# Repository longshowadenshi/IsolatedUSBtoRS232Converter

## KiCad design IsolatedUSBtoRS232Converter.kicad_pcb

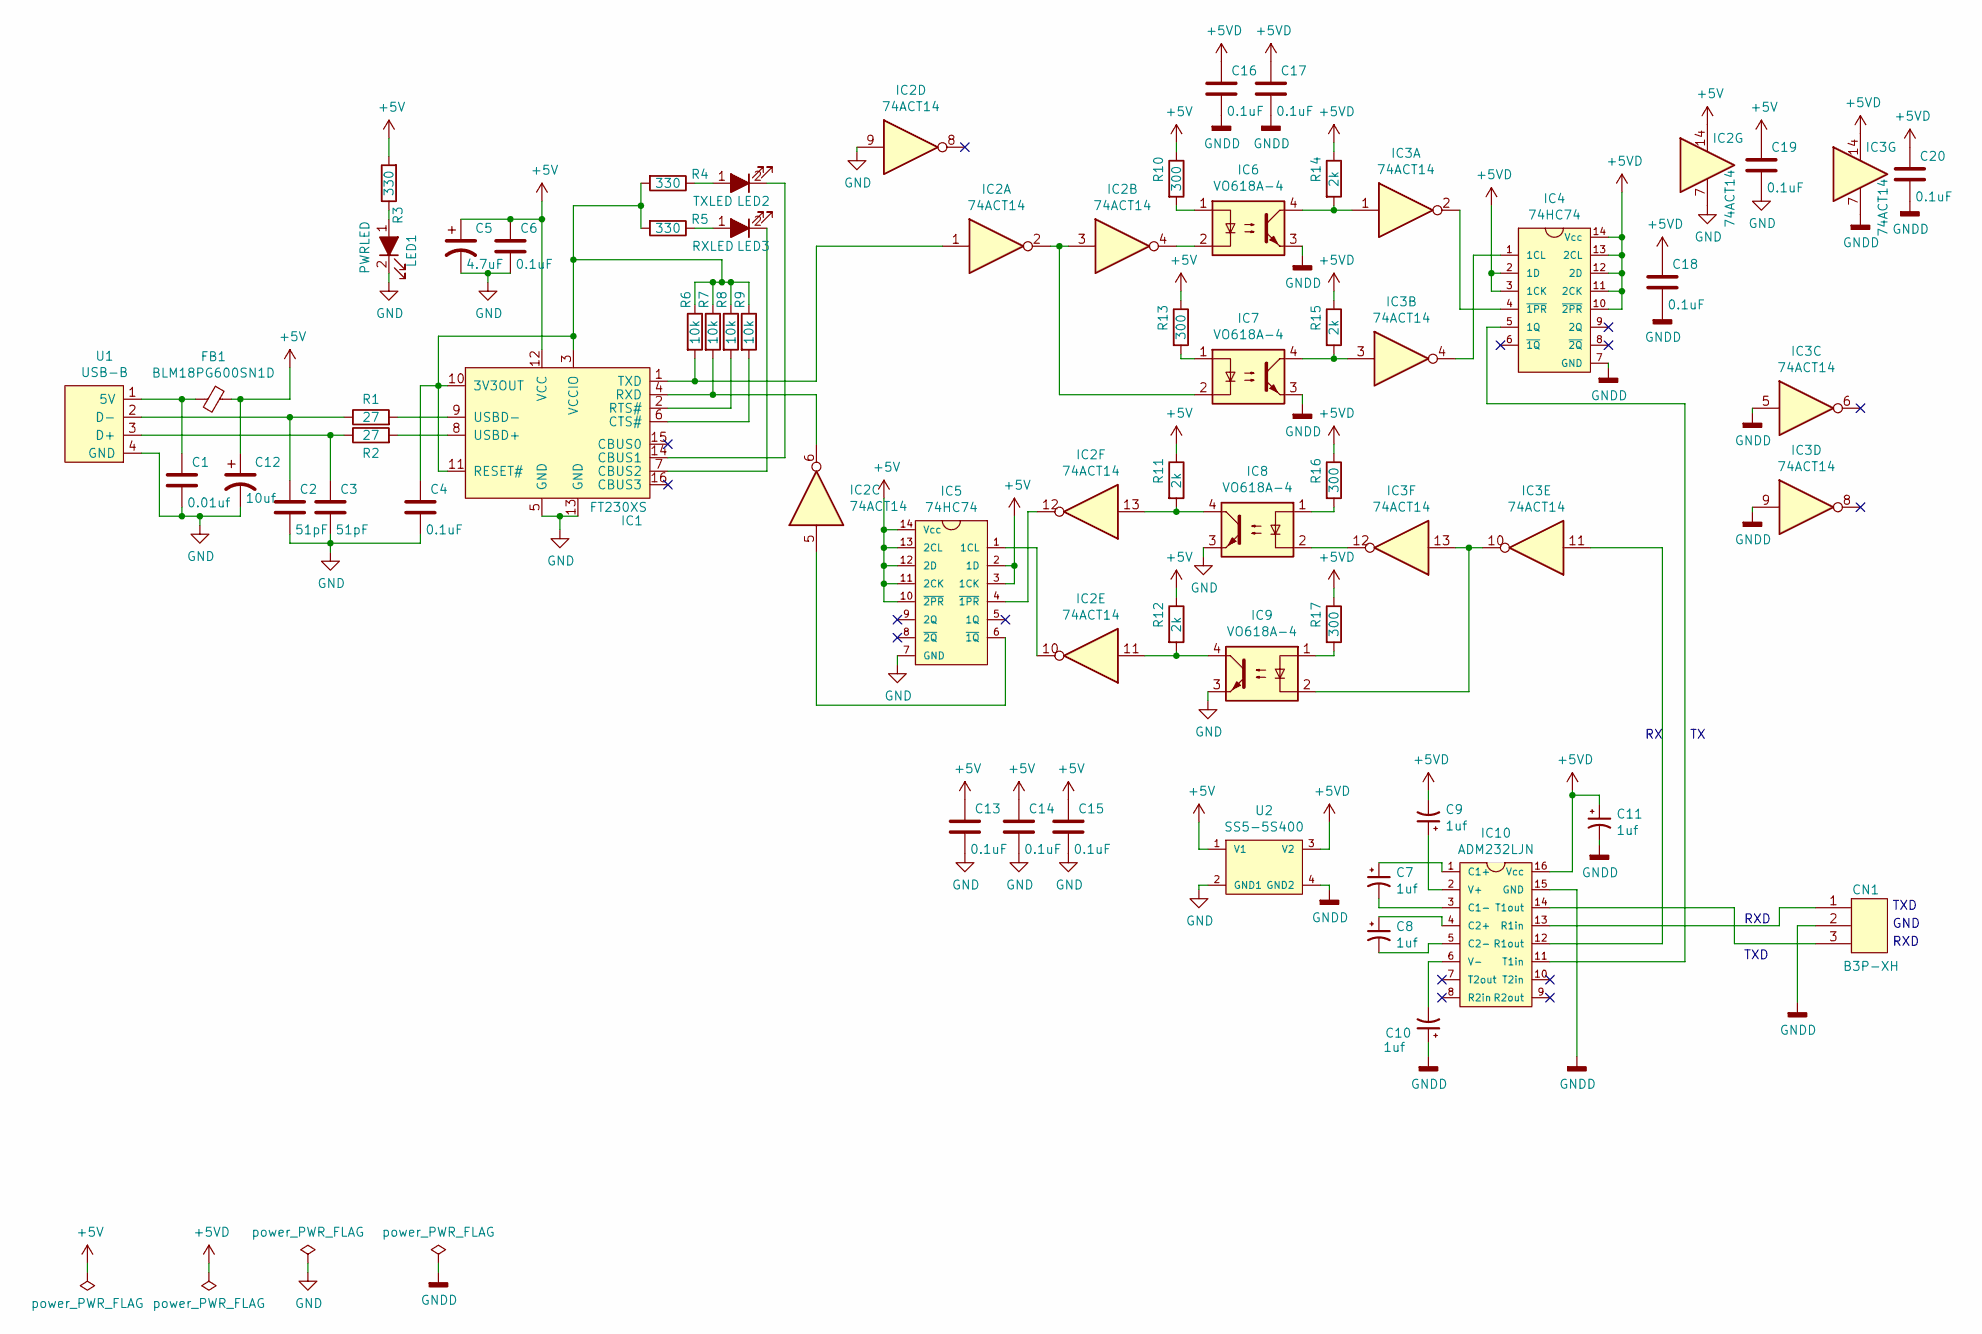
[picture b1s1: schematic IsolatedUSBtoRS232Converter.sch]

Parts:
C1: 0.01uf; C1608C0G1H682J
C2, C3: 51pF; C1608C0G1H682J
C4, C6, C13, C14, C15, C16, C17, C18, C19, C20: 0.1uF; C1608C0G1H682J
C5: 4.7uF; 10uF-16v
C7, C8, C9, C10, C11: 1uf; C-3mm
C12: 10uf; 10uF-16v
CN1: B3P-XH; S3B-XH-A
FB1: BLM18PG600SN1D; C1608C0G1H682J
IC1: FT230XS
IC2, IC3: 74ACT14; 74HC-14pins
IC4, IC5: 74HC74; 74HC-14pins
IC6, IC7, IC8, IC9: VO618A-4
IC10: ADM232LJN; 74HC-16pins
LED1: PWRLED; led-os
LED2: TXLED; led-os
LED3: RXLED; led-os
R1, R2: 27; C1608C0G1H682J
R3, R4, R5: 330; R
R6, R7, R8, R9: 10k; C1608C0G1H682J
R10, R13, R16, R17: 300; C1608C0G1H682J
R11, R12, R14, R15: 2k; C1608C0G1H682J
U1: USB-B
U2: SS5-5S400

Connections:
+5V: C5.1, C6.1, C12.1, C13.1, C14.1, C15.1, C19.1, FB1.1, IC1.12 (VCC), IC2.14, IC5.2 (1D), IC5.3 (1CK), IC5.10 (~2PR), IC5.11 (2CK), IC5.12 (2D), IC5.13 (2CL), IC5.14 (Vcc), R3.2, R10.1, R11.1, R12.1, R13.1, U2.1 (V1)
+5VD: C9.2, C11.1, C16.1, C17.1, C18.1, C20.1, IC3.14, IC4.2 (1D), IC4.3 (1CK), IC4.10 (~2PR), IC4.11 (2CK), IC4.12 (2D), IC4.13 (2CL), IC4.14 (Vcc), IC10.16 (Vcc), R14.1, R15.1, R16.1, R17.1, U2.3 (V2)
GND: C1.2, C2.2, C3.2, C4.2, C5.2, C6.2, C12.2, C13.2, C14.2, C15.2, C19.2, IC1.5 (GND), IC1.13 (GND), IC2.7, IC2.9, IC5.7 (GND), IC8.3, IC9.3, LED1.2, U1.4 (GND), U2.2 (GND1)
GNDD: C10.1, C11.2, C16.2, C17.2, C18.2, C20.2, CN1.2, IC3.5, IC3.7, IC3.9, IC4.7 (GND), IC6.3, IC7.3, IC10.15 (GND), U2.4 (GND2)
unnamed: C1.1, FB1.2, U1.1 (5V)
unnamed: C2.1, R1.1, U1.2 (D-)
unnamed: C3.1, R2.1, U1.3 (D+)
unnamed: C4.1, IC1.3 (VCCIO), IC1.10 (3V3OUT), IC1.11 (RESET#), R4.2, R5.2, R6.1, R7.1, R8.1, R9.1
unnamed: C7.1, IC10.1 (C1+)
unnamed: C7.2, IC10.3 (C1-)
unnamed: C8.1, IC10.4 (C2+)
unnamed: C8.2, IC10.5 (C2-)
unnamed: C9.1, IC10.2 (V+)
unnamed: C10.2, IC10.6 (V-)
unnamed: CN1.1, IC10.13 (R1in)
unnamed: CN1.3, IC10.14 (T1out)
unnamed: IC1.1 (TXD), IC2.1, R6.2
unnamed: IC1.2 (RTS#), R8.2
unnamed: IC1.4 (RXD), IC2.6, R7.2
unnamed: IC1.6 (CTS#), R9.2
unnamed: IC1.7 (CBUS2), LED3.2
unnamed: IC1.8 (USBD+), R2.2
unnamed: IC1.9 (USBD-), R1.2
unnamed: IC1.14 (CBUS1), LED2.2
unnamed: IC2.2, IC2.3, IC7.2
unnamed: IC2.4, IC6.2
unnamed: IC2.5, IC5.6 (~1Q)
unnamed: IC2.10, IC5.1 (1CL)
unnamed: IC2.11, IC9.4, R12.2
unnamed: IC2.12, IC5.4 (~1PR)
unnamed: IC2.13, IC8.4, R11.2
unnamed: IC3.1, IC6.4, R14.2
unnamed: IC3.2, IC4.4 (~1PR)
unnamed: IC3.3, IC7.4, R15.2
unnamed: IC3.4, IC4.1 (1CL)
unnamed: IC3.10, IC3.13, IC9.2
unnamed: IC3.12, IC8.2
unnamed: IC6.1, R10.2
unnamed: IC7.1, R13.2
unnamed: IC8.1, R16.2
unnamed: IC9.1, R17.2
unnamed: IC4.5 (1Q), IC10.11 (T1in)
unnamed: IC3.11, IC10.12 (R1out)
unnamed: LED1.1, R3.1
unnamed: LED2.1, R4.1
unnamed: LED3.1, R5.1

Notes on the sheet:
RXD
TXD
GND

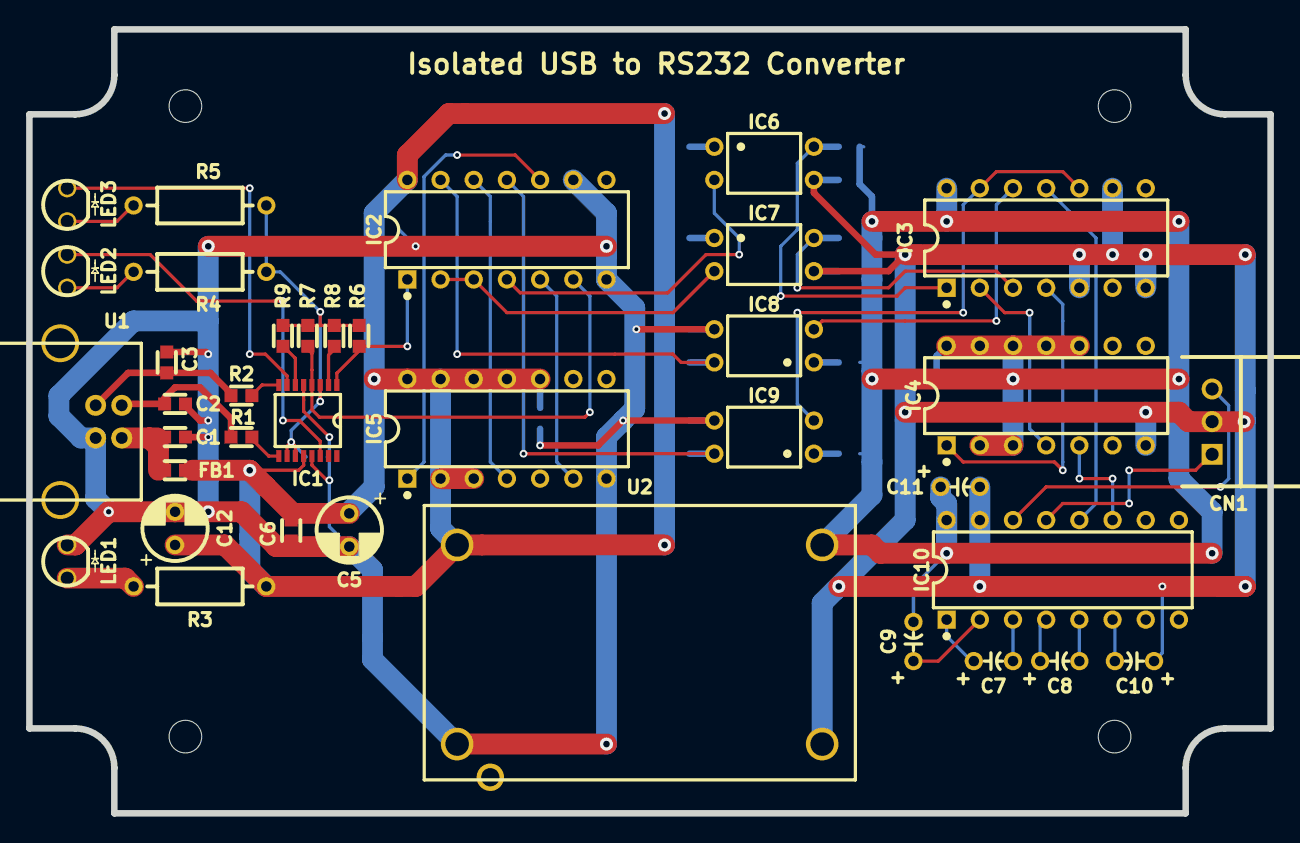
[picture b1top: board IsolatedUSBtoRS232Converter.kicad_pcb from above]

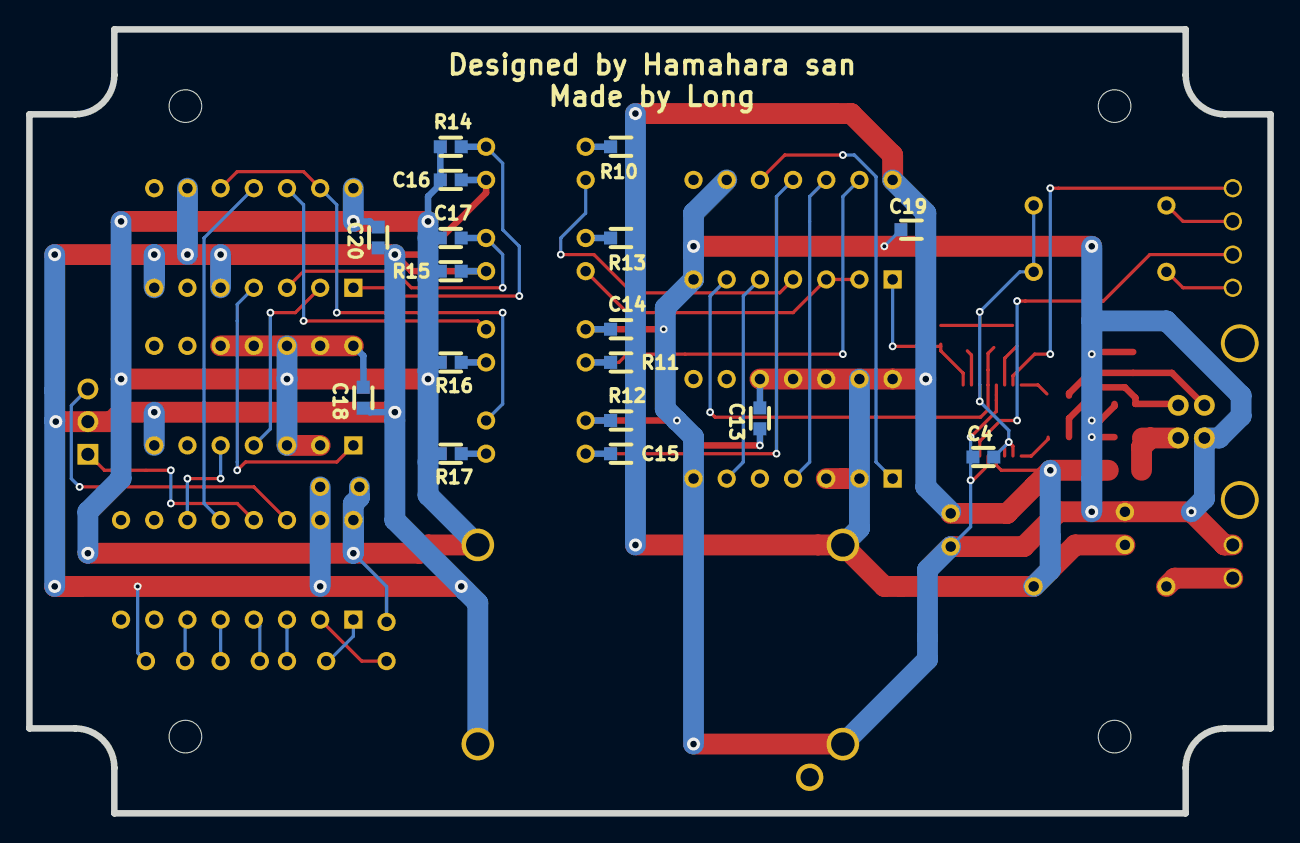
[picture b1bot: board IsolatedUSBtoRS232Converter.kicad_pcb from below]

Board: 2 copper layers, 95.0 x 60.0 mm, 54 parts (17 on the bottom side), 46 nets.
